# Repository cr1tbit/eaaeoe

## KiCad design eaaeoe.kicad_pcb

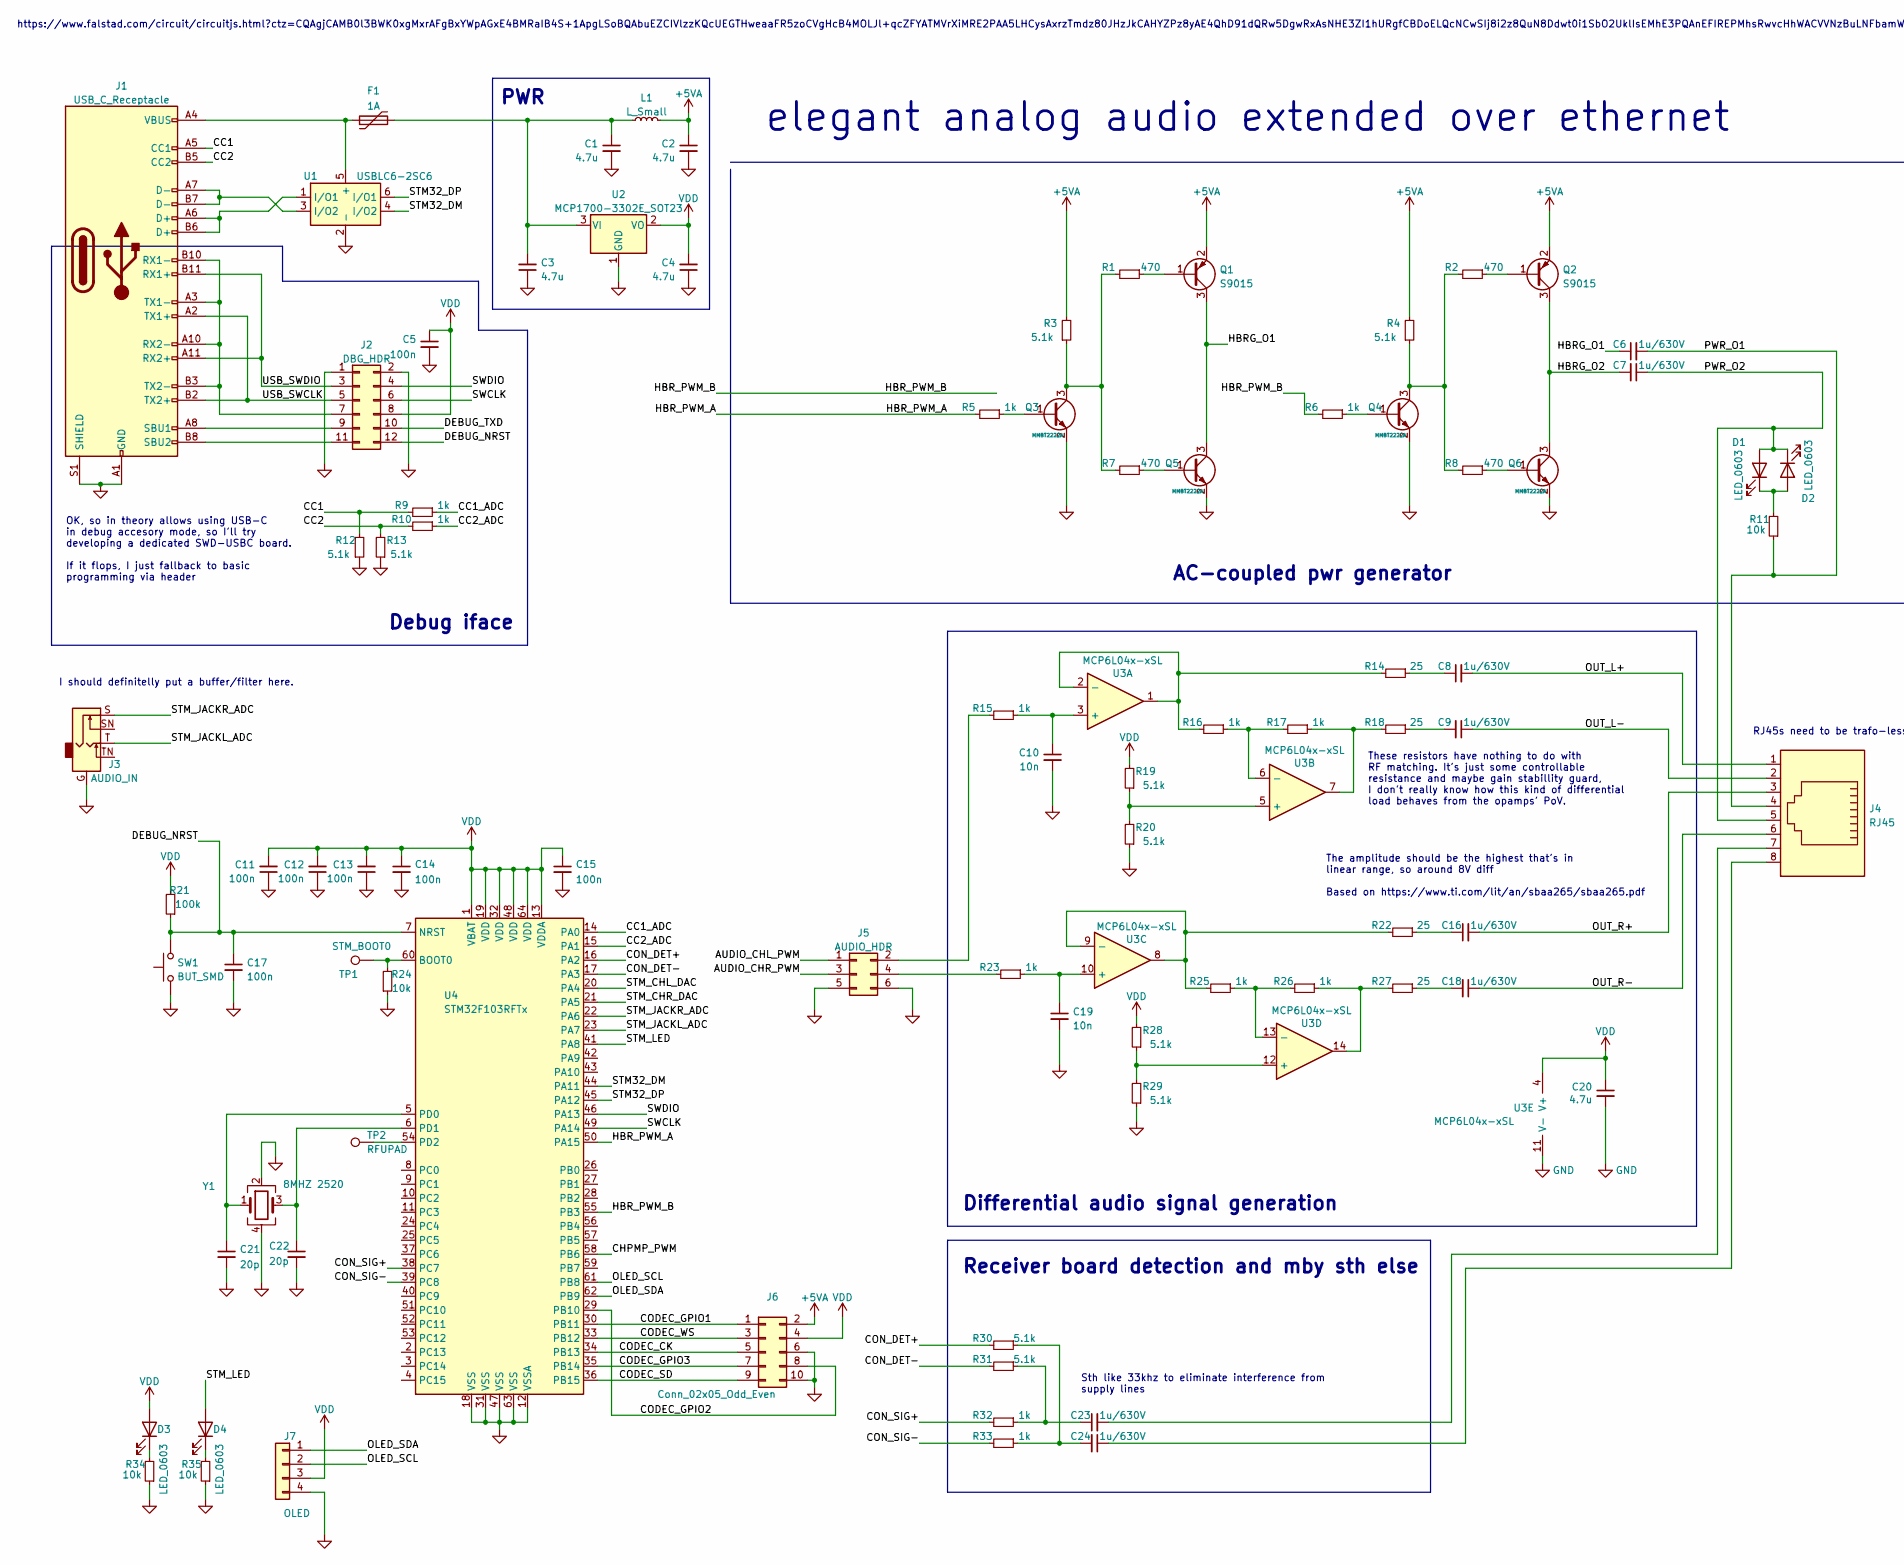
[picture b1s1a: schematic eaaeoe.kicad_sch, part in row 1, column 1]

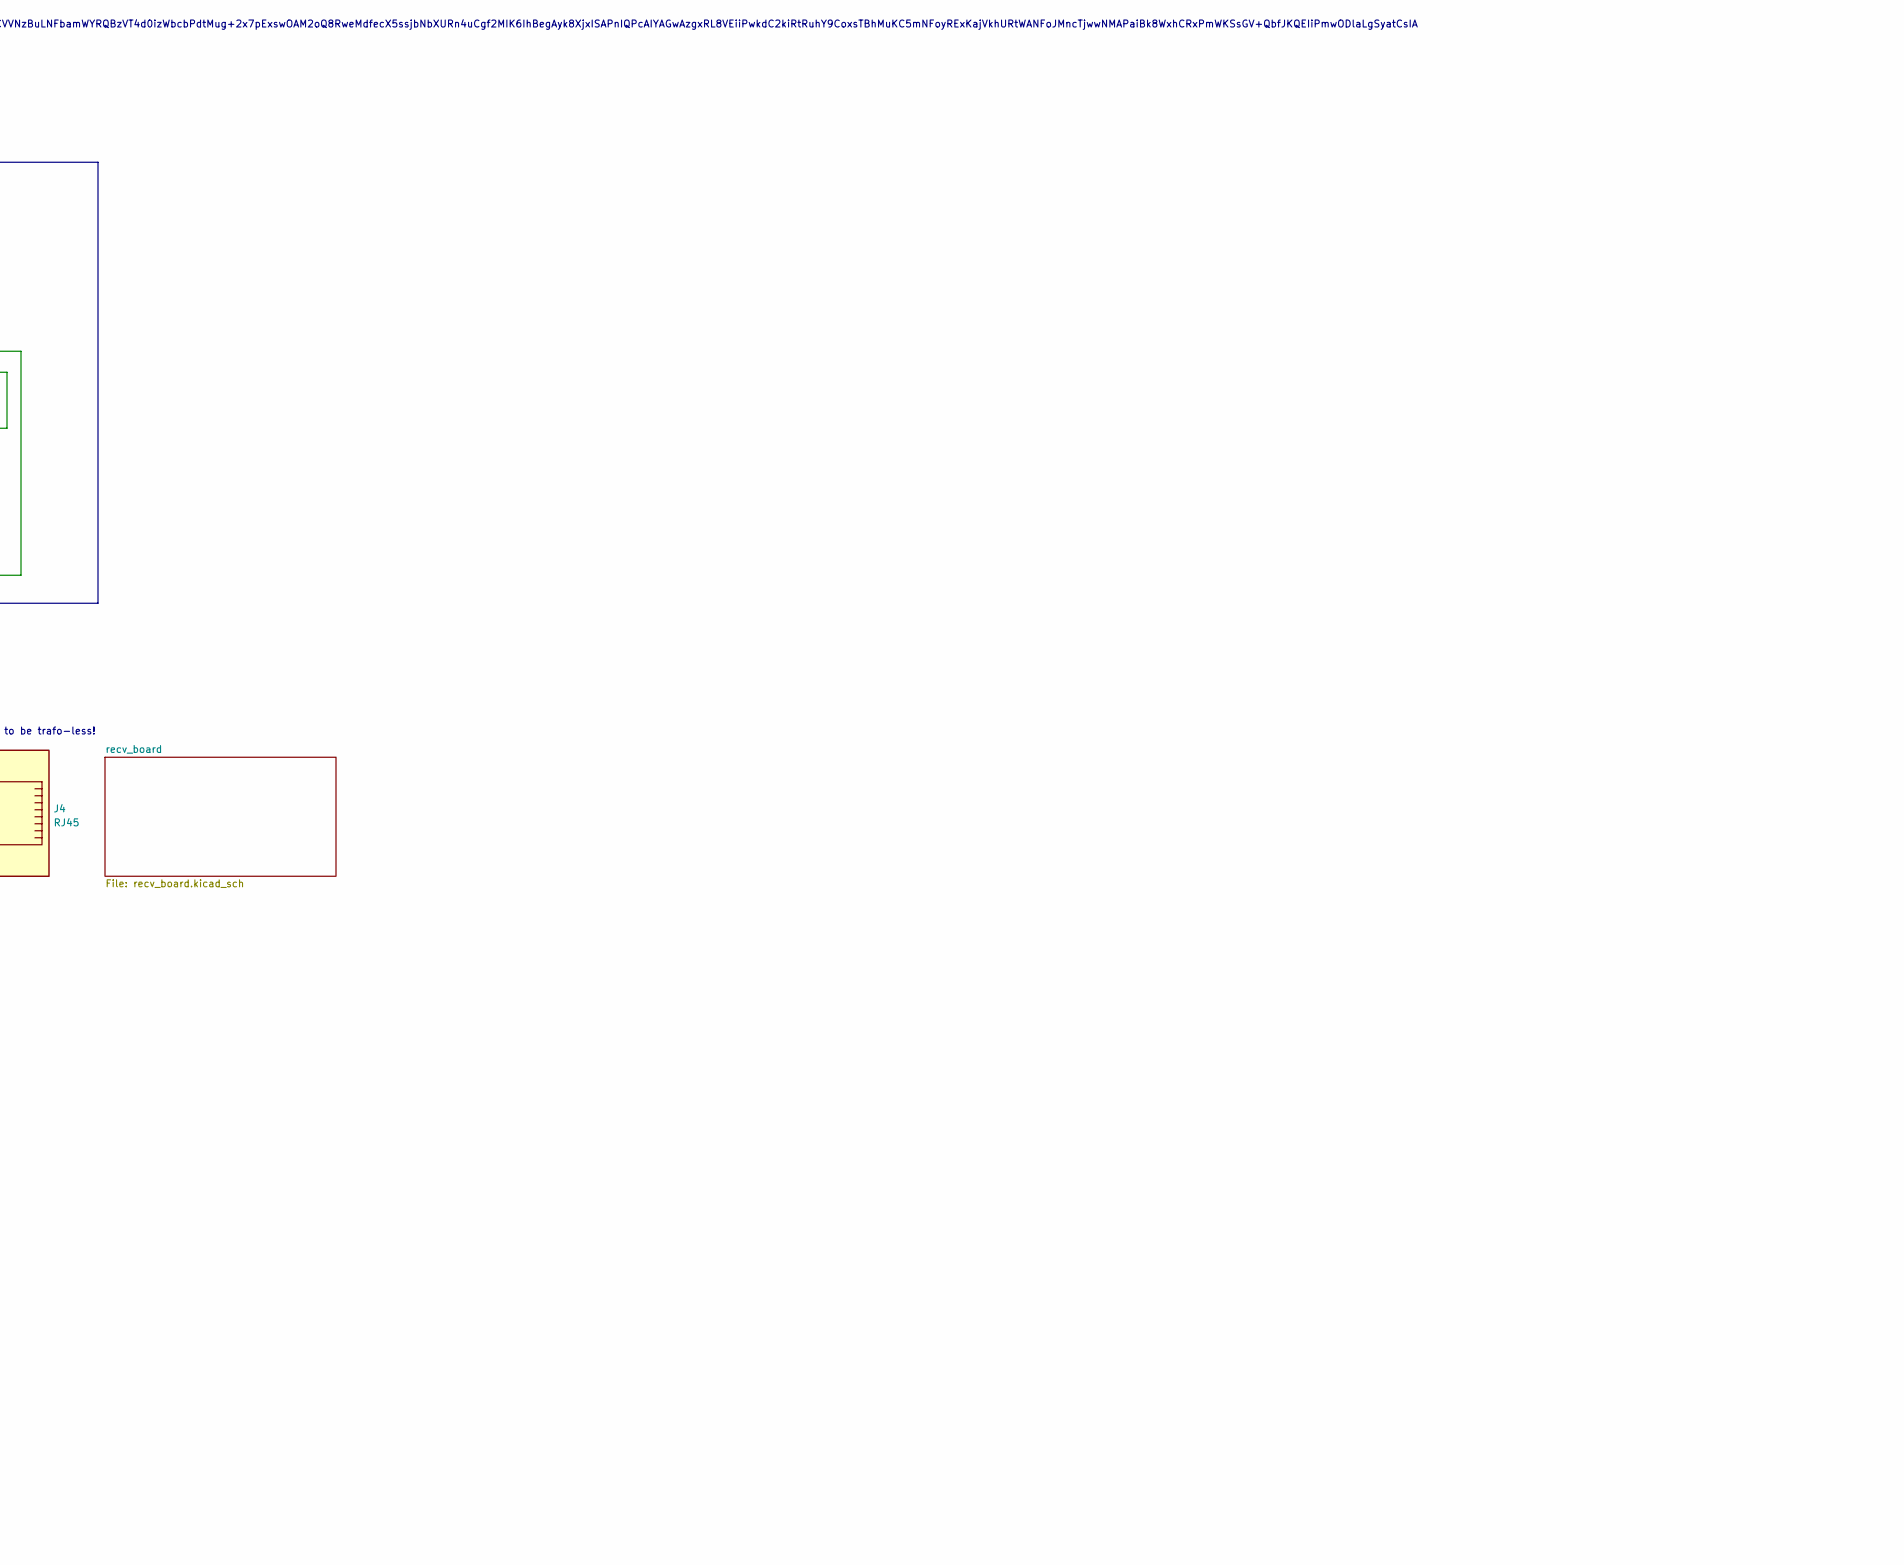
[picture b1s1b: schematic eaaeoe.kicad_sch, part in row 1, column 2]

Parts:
C1, C2, C3, C4: 4.7u; C_0402_1005Metric
C5, C11, C12, C13, C14, C15, C17: 100n; C_0402_1005Metric
C6, C7, C8, C9, C16, C18: 1u/630V; C_Disc_D10.0mm_W2.5mm_P5.00mm
C10, C19: 10n; C_0402_1005Metric
C20: 4.7u; C_0402_1005Metric; LCSC C12530
C21, C22: 20p; C_0402_1005Metric
C23, C24: 1u/630V; C_0402_1005Metric
D1, D2, D3, D4: LED_0603; LED_0603_1608Metric_Pad1.05x0.95mm_HandSolder
F1: 1A; R_1210_3225Metric_Pad1.30x2.65mm_HandSolder
J1: USB_C_Receptacle; USB_C_Receptacle_Amphenol_12401610E4-2A
J2: DBG_HDR; PinSocket_2x06_P2.54mm_Vertical
J3: AUDIO_IN; Jack_3.5mm_CUI_SJ1-3535NG_Horizontal_CircularHoles
J4: RJ45; RJ45_OST_PJ012-8P8CX_Vertical
J5: AUDIO_HDR; PinSocket_2x03_P2.54mm_Vertical
J6: Conn_02x05_Odd_Even; PinHeader_2x05_P2.54mm_Vertical
J7: OLED; PinSocket_1x04_P2.54mm_Vertical
L1: L_Small; L_1206_3216Metric
Q1, Q2: S9015; SOT-23
Q3, Q4, Q5, Q6: MMBT2222A; SOT-23
R1, R2, R7, R8: 470; R_0402_1005Metric
R3, R4, R12, R13, R19, R20, R28, R29, R30, R31: 5.1k; R_0402_1005Metric
R5, R6, R9, R10, R15, R16, R17, R23, R25, R26, R32, R33: 1k; R_0402_1005Metric
R11, R34, R35: 10k; R_0402_1005Metric; LCSC C25117
R14, R18, R22, R27: 25; R_0402_1005Metric
R21: 100k; R_0402_1005Metric
R24: 10k; R_0402_1005Metric
SW1: BUT_SMD; SW_SPST_TL3342
TP1: STM_BOOT0; TestPoint_Pad_D1.0mm
TP2: RFUPAD; TestPoint_Pad_D1.0mm
U1: USBLC6-2SC6; SOT-23-6
U2: MCP1700-3302E_SOT23; SOT-23
U3: MCP6L04x-xSL; SOIC-14_3.9x8.7mm_P1.27mm; LCSC C626833
U4: STM32F103RFTx; LQFP-64_10x10mm_P0.5mm
Y1: 8MHZ 2520; Crystal_SMD_2520-4Pin_2.5x2.0mm

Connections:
+5VA: C2.1, J6.2, L1.2, Q1.2 (E), Q2.2 (E), R3.2, R4.2
/AUDIO_CHL_PWM: J5.1
/AUDIO_CHR_PWM: J5.3
/CC1: J1.A5 (CC1), R9.2, R12.2
/CC1_ADC: R9.1, U4.14 (PA0)
/CC2: J1.B5 (CC2), R10.2, R13.2
/CC2_ADC: R10.1, U4.15 (PA1)
/CHPMP_PWM: U4.58 (PB6)
/CODEC_CK: J6.5, U4.34 (PB13)
/CODEC_GPIO1: J6.1, U4.30 (PB11)
/CODEC_GPIO2: J6.8, U4.29 (PB10)
/CODEC_GPIO3: J6.7, U4.35 (PB14)
/CODEC_SD: J6.9, U4.36 (PB15)
/CODEC_WS: J6.3, U4.33 (PB12)
/CON_DET+: R30.2, U4.16 (PA2)
/CON_DET-: R31.2, U4.17 (PA3)
/CON_SIG+: R32.2, U4.38 (PC7)
/CON_SIG-: R33.2, U4.39 (PC8)
/DEBUG_NRST: C17.1, J2.12, R21.1, SW1.2, U4.7 (NRST)
/DEBUG_TXD: J2.10
/HBRG_O1: C6.1, Q1.3 (C), Q5.3 (C)
/HBRG_O2: C7.2, Q2.3 (C), Q6.3 (C)
/HBR_PWM_A: R5.2, U4.50 (PA15)
/HBR_PWM_B: R6.2, U4.55 (PB3)
/OLED_SCL: J7.2, U4.61 (PB8)
/OLED_SDA: J7.1, U4.62 (PB9)
/OUT_L+: C8.2, J4.1
/OUT_L-: C9.1, J4.2
/OUT_R+: C16.2, J4.3
/OUT_R-: C18.1, J4.6
/PWR_O1: C6.2, J4.4, R11.1
/PWR_O2: C7.1, D1.2 (A), D2.1 (K), J4.5
/STM32_DM: U1.4 (I/O2), U4.44 (PA11)
/STM32_DP: U1.6 (I/O1), U4.45 (PA12)
/STM_CHL_DAC: U4.20 (PA4)
/STM_CHR_DAC: U4.21 (PA5)
/STM_JACKL_ADC: J3.T, U4.23 (PA7)
/STM_JACKR_ADC: J3.S, U4.22 (PA6)
/STM_LED: D4.2 (A), U4.41 (PA8)
/SWCLK: J2.6, U4.49 (PA14)
/SWDIO: J2.4, U4.46 (PA13)
/USB_SWCLK: J1.A2 (TX1+), J1.B2 (TX2+), J2.5
/USB_SWDIO: J1.A11 (RX2+), J1.B11 (RX1+), J2.3
GND: C1.2, C2.2, C3.1, C4.1, C5.2, C10.2, C11.1, C12.1, C13.1, C14.2, C15.2, C17.2, C19.2, C20.2, C21.2, C22.2, J1.A1 (GND), J1.A12 (GND), J1.B1 (GND), J1.B12 (GND), J1.S1 (SHIELD), J2.1, J2.2, J3.G, J5.5, J5.6, J6.6, J6.10, J7.4, Q3.2 (E), Q4.2 (E), Q5.2 (E), Q6.2 (E), R12.1, R13.1, R20.1, R24.1, R29.1, R34.1, R35.1, SW1.1, U1.2 (-), U2.1 (GND), U3.11 (V-), U4.12 (VSSA), U4.18 (VSS), U4.31 (VSS), U4.47 (VSS), U4.63 (VSS), Y1.2, Y1.4
unnamed: C1.1, C3.2, F1.2, L1.1, U2.3 (VI)
unnamed: C8.1, R14.1
unnamed: C9.2, R18.1
unnamed: C10.1, R15.1, U3.3 (+)
unnamed: C16.1, R22.1
unnamed: C18.2, R27.1
unnamed: C19.1, R23.1, U3.10 (+)
unnamed: C21.1, U4.5 (PD0), Y1.1
unnamed: C22.1, U4.6 (PD1), Y1.3
unnamed: C23.1, R31.1, R32.1
unnamed: C23.2, J4.7
unnamed: C24.1, J4.8
unnamed: C24.2, R30.1, R33.1
unnamed: D1.1 (K), D2.2 (A), R11.2
unnamed: D3.1 (K), R34.2
unnamed: D4.1 (K), R35.2
unnamed: F1.1, J1.A4 (VBUS), J1.A9 (VBUS), J1.B4 (VBUS), J1.B9 (VBUS), U1.5 (+)
unnamed: J1.A6 (D+), J1.B6 (D+), U1.1 (I/O1)
unnamed: J1.A7 (D-), J1.B7 (D-), U1.3 (I/O2)
unnamed: J1.A8 (SBU1), J2.9
unnamed: J1.A3 (TX1-), J1.A10 (RX2-), J1.B3 (TX2-), J1.B10 (RX1-), J2.7
unnamed: J1.B8 (SBU2), J2.11
unnamed: J5.2, R15.2
unnamed: J5.4, R23.2
unnamed: Q1.1 (B), R1.1
unnamed: Q2.1 (B), R2.1
unnamed: Q3.1 (B), R5.1
unnamed: Q3.3 (C), R1.2, R3.1, R7.2
unnamed: Q4.1 (B), R6.1
unnamed: Q4.3 (C), R2.2, R4.1, R8.2
unnamed: Q5.1 (B), R7.1
unnamed: Q6.1 (B), R8.1
unnamed: R14.2, R16.2, U3.1, U3.2 (-)
unnamed: R16.1, R17.2, U3.6 (-)
unnamed: R17.1, R18.2, U3.7
unnamed: R19.1, R20.2, U3.5 (+)
unnamed: R22.2, R25.2, U3.8, U3.9 (-)
unnamed: R24.2, TP1.1, U4.60 (BOOT0)
unnamed: R25.1, R26.2, U3.13 (-)
unnamed: R26.1, R27.2, U3.14
unnamed: R28.1, R29.2, U3.12 (+)
unnamed: TP2.1, U4.54 (PD2)
VDD: C4.2, C5.1, C11.2, C12.2, C13.2, C14.1, C15.1, C20.1, D3.2 (A), J2.8, J6.4, J7.3, R19.2, R21.2, R28.2, U2.2 (VO), U3.4 (V+), U4.1 (VBAT), U4.13 (VDDA), U4.19 (VDD), U4.32 (VDD), U4.48 (VDD), U4.64 (VDD)

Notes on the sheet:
I should definitelly put a buffer/filter here.
Debug iface
OK, so in theory allows using USB-C in debug accesory mode, so I'll try developing a dedicated SWD-USBC board. If it flops, I just fallback to basic programming via header
AC-coupled pwr generator
https://www.falstad.com/circuit/circuitjs.html?ctz=CQAgjCAMB0l3BWK0xgMxrAFgBxYWpAGxE4BMRaIB4S+1ApgLSoBQAbuEZCIVlzzKQcUEGTHweaaFR5zoCVgHcB4MOLJl+qcZFYATMVrXiMRE2PAA5LHCysAxrzTmdz80JHzJkCAHYZPz8yAE4QhD91dQRw5DgwRxAsNHE3ZI1hURgfCBDoELQcNCwSIj8i2z8QuN8Ddwt0i1SbO2UklIsEMhE3PQAnEFIREPMhsRwvcHhWACVVNzBuLN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
Receiver board detection and mby sth else
elegant analog audio extended over ethernet
PWR
Differential audio signal generation
The amplitude should be the highest that's in linear range, so around 8V diff Based on https://www.ti.com/lit/an/sbaa265/sbaa265.pdf
These resistors have nothing to do with RF matching. It's just some controllable resistance and maybe gain stabillity guard, I don't really know how this kind of differential load behaves from the opamps' PoV.
RJ45s need to be trafo-less!
Sth like 33khz to eliminate interference from supply lines

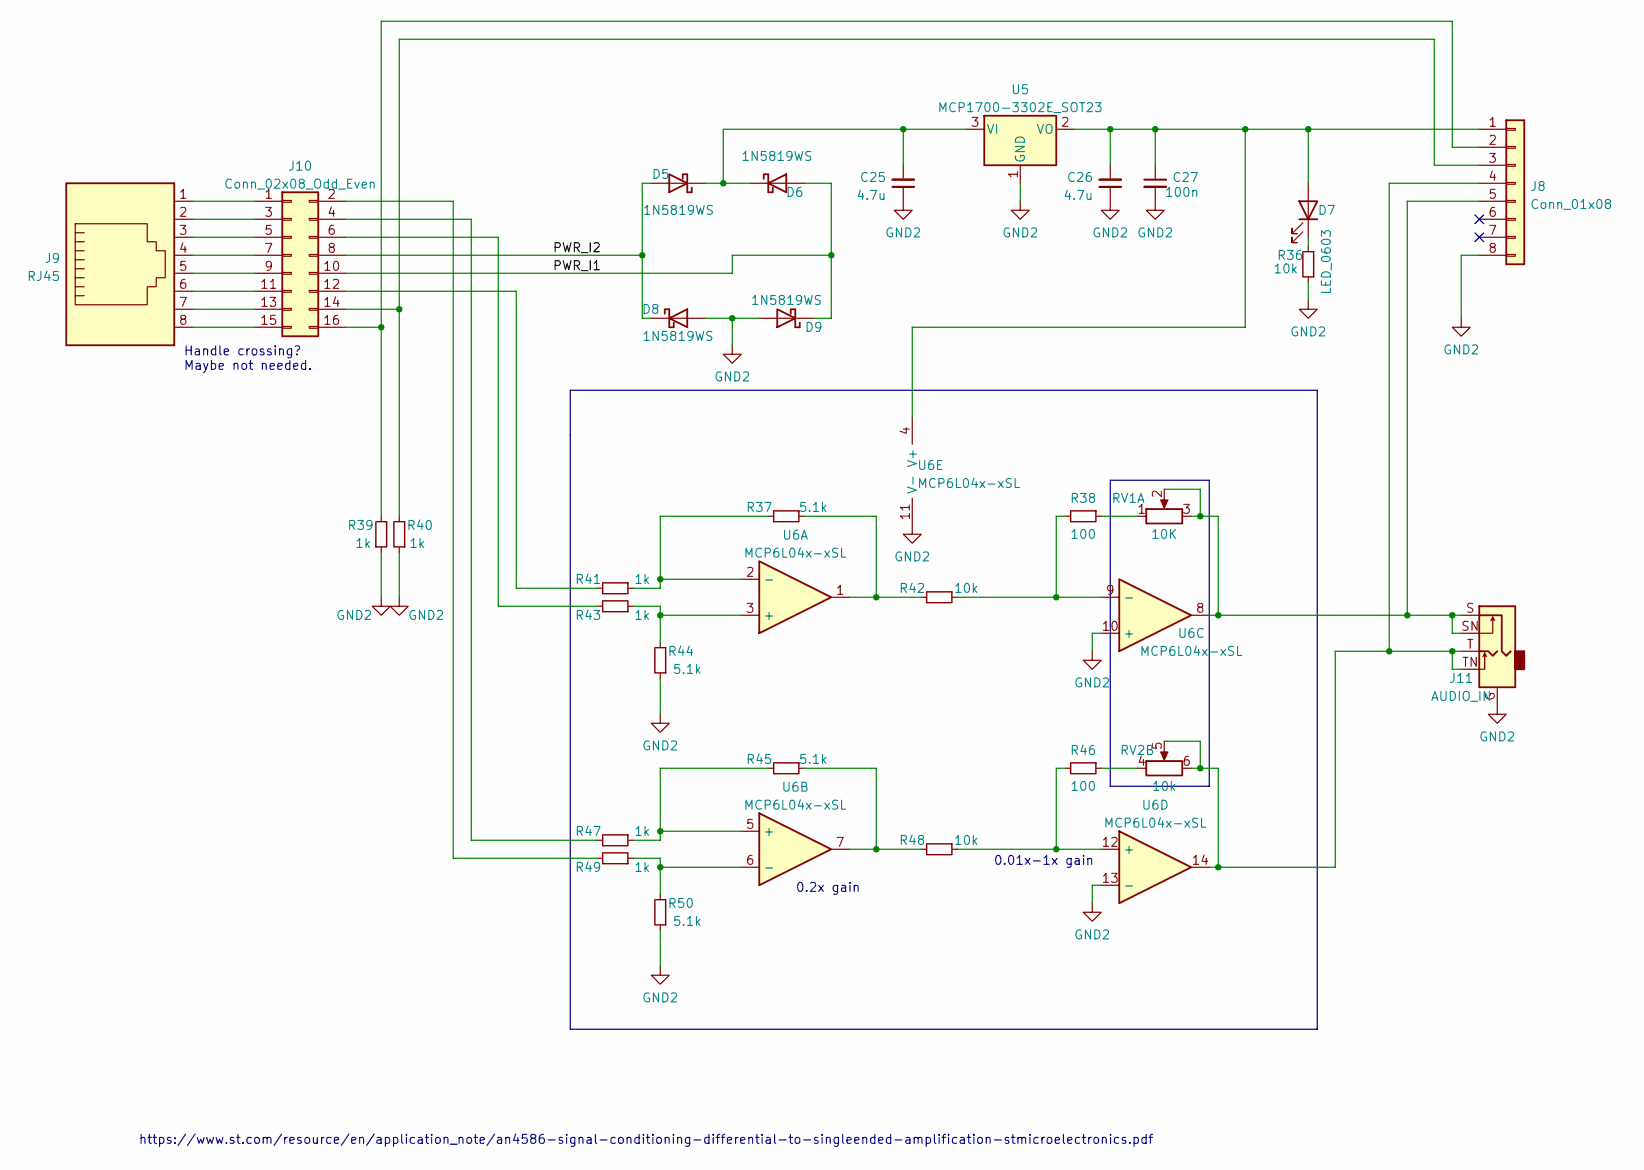
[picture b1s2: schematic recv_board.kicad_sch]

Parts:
C25, C26: 4.7u; C_0402_1005Metric
C27: 100n; C_0402_1005Metric
D5, D6, D8, D9: 1N5819WS; D_SOD-323
D7: LED_0603; LED_0603_1608Metric_Pad1.05x0.95mm_HandSolder
J8: Conn_01x08; PinHeader_1x08_P2.54mm_Vertical
J9: RJ45; RJ45_OST_PJ012-8P8CX_Vertical
J10: Conn_02x08_Odd_Even; PinSocket_2x08_P2.54mm_Vertical
J11: AUDIO_IN; Jack_3.5mm_CUI_SJ1-3535NG_Horizontal_CircularHoles
R36: 10k; R_0402_1005Metric; LCSC C25117
R37, R44, R45, R50: 5.1k; R_0402_1005Metric
R38, R46: 100; R_0402_1005Metric
R39, R40, R41, R43, R47, R49: 1k; R_0402_1005Metric
R42, R48: 10k; R_0402_1005Metric
RV1: 10K; Potentiometer_Alps_RK163_Dual_Horizontal
RV2: 10k; Potentiometer_Alps_RK163_Dual_Horizontal
U5: MCP1700-3302E_SOT23; SOT-23
U6: MCP6L04x-xSL; SOIC-14_3.9x8.7mm_P1.27mm

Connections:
/recv_board/PWR_I1: D6.2 (A), D9.1 (K), J10.10
/recv_board/PWR_I2: D5.2 (A), D8.1 (K), J10.8
GND2: C25.1, C26.1, C27.2, D8.2 (A), D9.2 (A), J8.8, J11.G, R36.1, R39.1, R40.1, R44.1, R50.1, U5.1 (GND), U6.10 (+), U6.11 (V-), U6.13 (-)
unnamed: C25.2, D5.1 (K), D6.1 (K), U5.3 (VI)
unnamed: C26.2, C27.1, D7.2 (A), J8.1, U5.2 (VO), U6.4 (V+)
unnamed: D7.1 (K), R36.2
unnamed: J9.1, J10.1
unnamed: J10.2, R49.2
unnamed: J9.2, J10.3
unnamed: J10.4, R47.2
unnamed: J9.3, J10.5
unnamed: J10.6, R43.2
unnamed: J9.4, J10.7
unnamed: J9.5, J10.9
unnamed: J9.6, J10.11
unnamed: J10.12, R41.2
unnamed: J9.7, J10.13
unnamed: J8.3, J10.14, R40.2
unnamed: J9.8, J10.15
unnamed: J8.2, J10.16, R39.2
unnamed: J8.5, J11.S, J11.SN, RV1.2, RV1.3, U6.8
unnamed: J8.4, J11.T, J11.TN, RV2.5, RV2.6, U6.14
unnamed: R37.1, R42.2, U6.1
unnamed: R37.2, R41.1, U6.2 (-)
unnamed: R38.1, RV1.1
unnamed: R38.2, R42.1, U6.9 (-)
unnamed: R43.1, R44.2, U6.3 (+)
unnamed: R45.1, R48.2, U6.7
unnamed: R45.2, R47.1, U6.5 (+)
unnamed: R46.1, RV2.4
unnamed: R46.2, R48.1, U6.12 (+)
unnamed: R49.1, R50.2, U6.6 (-)

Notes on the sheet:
https://www.st.com/resource/en/application_note/an4586-signal-conditioning-differential-to-singleended-amplification-stmicroelectronics.pdf
0.2x gain
0.01x-1x gain
Handle crossing? Maybe not needed.

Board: 2 copper layers, 116 parts (0 on the bottom side), 112 nets, no tracks yet.

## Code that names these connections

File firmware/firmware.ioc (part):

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Mcu.Name=STM32F103R(F-G)Tx
Mcu.Package=LQFP64
Mcu.UserName=STM32F103RFTx
PA0-WKUP.GPIOParameters=GPIO_Label
PA0-WKUP.GPIO_Label=CC1_ADC
PA0-WKUP.Signal=ADCx_IN0
PA1.GPIOParameters=GPIO_Label
PA1.GPIO_Label=CC2_ADC
PA1.Signal=ADCx_IN1
PA10.GPIOParameters=GPIO_Label
PA10.GPIO_Label=DEBUG_RXD
PA10.Mode=Asynchronous
PA10.Signal=USART1_RX
PA11.Mode=Device
PA11.Signal=USB_DM
PA12.Mode=Device
PA12.Signal=USB_DP
PA13.Mode=Serial_Wire
PA13.Signal=SYS_JTMS-SWDIO
PA14.Mode=Serial_Wire
PA14.Signal=SYS_JTCK-SWCLK
PA15.GPIOParameters=GPIO_Label
PA15.GPIO_Label=HBR_PWM_A
PA15.Signal=S_TIM2_CH1_ETR
PA2.GPIOParameters=GPIO_Label
PA2.GPIO_Label=CON_DET+
PA2.Signal=ADCx_IN2
PA3.GPIOParameters=GPIO_Label
PA3.GPIO_Label=CON_DET-
PA3.Signal=ADCx_IN3
PA4.GPIOParameters=GPIO_Label
PA4.GPIO_Label=STM_CHL_DAC
PA4.Signal=COMP_DAC1_group
PA5.GPIOParameters=GPIO_Label
PA5.GPIO_Label=STM_CHR_DAC
PA5.Signal=COMP_DAC2_group
PA6.GPIOParameters=GPIO_Label
PA6.GPIO_Label=STM_JACKR_ADC
PA6.Signal=ADCx_IN6
PA7.GPIOParameters=GPIO_Label
PA7.GPIO_Label=STM_JACKL_ADC
PA7.Signal=ADCx_IN7
PA8.GPIOParameters=GPIO_Label
PA8.GPIO_Label=STM_LED
PA8.Signal=GPIO_Output
PA9.GPIOParameters=GPIO_Label
PA9.GPIO_Label=DEBUG_TXD
PA9.Mode=Asynchronous
PA9.Signal=USART1_TX
PB12.GPIOParameters=GPIO_Label
PB12.GPIO_Label=CODEC_WS
PB12.Mode=Half_Duplex_Master_TX
PB12.Signal=I2S2_WS
PB13.GPIOParameters=GPIO_Label
PB13.GPIO_Label=CODEC_CK
PB13.Mode=Half_Duplex_Master_TX
PB13.Signal=I2S2_CK
PB15.GPIOParameters=GPIO_Label
PB15.GPIO_Label=CODEC_SD
PB15.Mode=Half_Duplex_Master_TX
PB15.Signal=I2S2_SD
PB3.GPIOParameters=GPIO_Label
PB3.GPIO_Label=HBR_PWM_B
PB3.Signal=S_TIM2_CH2
PB6.GPIOParameters=GPIO_Label
PB6.GPIO_Label=CHGPMP_PWM
PB6.Signal=S_TIM4_CH1
PB8.GPIOParameters=GPIO_Label
PB8.GPIO_Label=OLED_SCL
PB8.Mode=I2C
PB8.Signal=I2C1_SCL
PB9.GPIOParameters=GPIO_Label
PB9.GPIO_Label=OLED_SDA
PB9.Mode=I2C
PB9.Signal=I2C1_SDA
PC6.GPIOParameters=GPIO_Label
PC6.GPIO_Label=CON_SIG-
PC6.Signal=S_TIM3_CH1
PC7.GPIOParameters=GPIO_Label
PC7.GPIO_Label=CON_SIG+
PC7.Signal=S_TIM3_CH2
PD0-OSC_IN.Mode=HSE-External-Oscillator
PD0-OSC_IN.Signal=RCC_OSC_IN
PD1-OSC_OUT.Mode=HSE-External-Oscillator
PD1-OSC_OUT.Signal=RCC_OSC_OUT
RCC.SYSCLKFreq_VALUE=72000000
RCC.SYSCLKSource=RCC_SYSCLKSOURCE_PLLCLK
board=custom

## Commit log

2022-11-21 add schematic concept and cube FW
2022-11-21 schematic = nicer
2022-11-29 finish schematic, add cubemx project, some initial layout
